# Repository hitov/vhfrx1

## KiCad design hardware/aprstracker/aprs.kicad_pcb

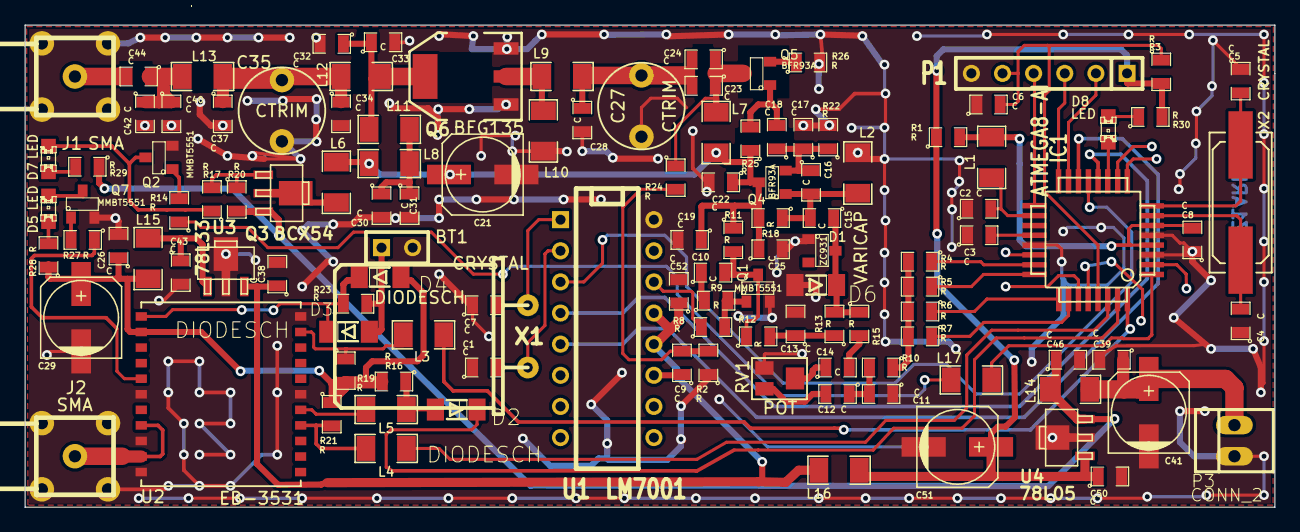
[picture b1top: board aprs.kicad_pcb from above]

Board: 2 copper layers, 102.0 x 39.3 mm, 122 parts (0 on the bottom side), 74 nets.

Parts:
ASTUB: VAL**; ASTUB
BT1: BATTERY; SIL-2
C1, C2, C3, C4, C5, C6, C7, C8, C9, C10, C11, C12, C13, C14, C15, C16, C17, C18, C19, C22, C23, C24, C25, C26, C28, C30, C31, C32, C33, C34, C37, C38, C39, C40, C42, C43, C44, C46, C50, C52: C; SM0805
C21, C41, C51: CAPAPOL; c_elec_6.3x4.5
C27, C35: CTRIM; TSC6
C29: CP1; c_elec_6.3x4.5
D1: ZC931; SOT23
D2, D3, D4: DIODESCH; MiniMelf
D5, D7, D8: LED; LED-0805
D6: VARICAP; MiniMelf
IC1: ATMEGA8-AI; TQFP32
J1, J2: SMA
L1, L2, L3, L4, L5, L6, L7, L8, L9, L10, L11, L12, L13, L14, L15, L16, L17: INDUCTOR; SM1206
P1: CONN_6; SIL-6
P3: CONN_2; PINHEAD1-2
Q1, Q2, Q7: MMBT5551; SOT23
Q3: BCX54; sot89
Q4, Q5: BFR93A; SOT23
Q6: BFG135; SOT223
R1, R2, R3, R4, R5, R6, R7, R8, R9, R10, R11, R12, R13, R14, R15, R16, R17, R18, R19, R20, R21, R22, R23, R24, R25, R26, R27, R28, R29, R30: R; SM0805
RV1: POT; MVR34
U1: LM7001; DIP-16__300
U2: EB-3531
U3: 78L33; sot89
U4: 78L05; sot89
X1: CRYSTAL; HC-18UH
X2: CRYSTAL; Q_49U3HMS

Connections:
3V3: C26.1, C29.1, D4.1, L15.2, R16.2, R19.2, R21.1, R28.1, U2.12
+5V: C38.1, C52.1, L16.2, U1.12, U1.13, U3.3
AUDIO: C11.2, C12.1, R10.2
CE: IC1.13, U1.3
CL: IC1.12, U1.4
DATA: IC1.14, U1.5
GND: BT1.2, C1.1, C2.1, C3.1, C4.1, C5.1, C6.1, C7.1, C8.1, C11.1, C13.2, C17.2, C19.2, C21.2, C22.2, C25.2, C26.2, C27.2, C28.2, C29.2, C30.2, C31.2, C32.2, C33.2, C34.2, C35.2, C37.2, C38.2, C39.2, C40.2, C41.2, C42.2, C43.2, C46.2, C50.2, C51.2, C52.2, D1.1, D6.1, IC1.3, IC1.5, IC1.21, J1.2, J1.3, J1.4, J1.5, J2.2, J2.3, J2.4, J2.5, L2.1, L10.2, P1.6, P3.1, Q1.2, Q2.2, Q6.1, Q6.3, Q7.2, R2.1, R22.2, R26.2, RV1.1, U1.16, U2.10, U2.18, U2.20, U2.21, U2.22, U3.2, U4.2
unnamed: R27.1, U2.15
unnamed: Q7.1, R27.2
unnamed: L3.2, R19.1, U2.9
unnamed: C39.1, C41.1, L14.1, P3.2
unnamed: L5.2, U2.5
unnamed: L4.2, R21.2, U2.4
unnamed: D3.2, D4.2, R23.1, U2.11
unnamed: BT1.1, D3.1, R23.2
unnamed: C43.1, L15.1, U3.1
unnamed: C40.1, C42.1, C44.1, L13.2
unnamed: C23.2, C24.2, C27.1, C28.1, L9.1
unnamed: C7.2, U1.1, X1.1
unnamed: C9.1, U1.11
unnamed: C13.1, R12.2, R13.1
unnamed: Q3.1, R17.2, R20.1
unnamed: C10.1, R9.1
unnamed: R8.1, U1.14
unnamed: IC1.26, R7.1
unnamed: C5.2, IC1.8, X2.2
unnamed: IC1.23, R4.1
unnamed: IC1.24, R5.1
unnamed: IC1.25, R6.1
unnamed: C3.2, IC1.20
unnamed: L17.2, R14.1
unnamed: C14.2, R15.2
unnamed: C14.1, RV1.2
unnamed: IC1.15, P1.2
unnamed: IC1.16, P1.3
unnamed: IC1.17, P1.4
unnamed: C6.2, IC1.29, P1.5, R3.1
unnamed: C4.2, IC1.7, X2.1
unnamed: L9.2, L10.1, Q6.2
unnamed: C18.2, Q5.1, R25.2
unnamed: Q5.2, R26.1
unnamed: C15.1, D1.3, D6.2, R13.2, R15.1
unnamed: D8.1, R30.1
unnamed: D8.2, IC1.11
unnamed: C23.1, C24.1, L7.2, Q5.3, R24.1
unnamed: D5.2, Q7.3
unnamed: Q2.1, R14.2
unnamed: D7.2, Q2.3, R17.1
unnamed: D7.1, R29.2
unnamed: L6.1, Q3.2
unnamed: C44.2, J1.1
unnamed: C9.2, R2.2, R24.2
unnamed: J2.1, U2.17, U2.19
unnamed: C8.2, IC1.4, IC1.6, L1.2, R1.2
unnamed: C2.2, IC1.18, L1.1
unnamed: R4.2, R5.2, R6.2, R7.2, R10.1
unnamed: Q1.1, R8.2, R9.2
unnamed: C10.2, Q1.3, R11.2, R12.1
unnamed: C15.2, C16.2, L2.2, Q4.1, R18.1
unnamed: C16.1, C17.1, C18.1, Q4.2, R22.1
unnamed: C12.2, RV1.3
unnamed: C1.2, U1.2, X1.2
unnamed: C34.1, C35.1, C37.1, L12.2, L13.1
unnamed: C32.1, C33.1, L11.2, L12.1, Q6.4
unnamed: C19.1, C21.1, C22.1, C25.1, L6.2, L7.1, L8.1, Q4.3, R11.1, R18.2, R25.1
unnamed: C30.1, C31.1, L8.2, L11.1
unnamed: D2.1, L5.1, R16.1
unnamed: D5.1, R28.2
RF_EN: IC1.1, L17.1
RF_PWR: IC1.32, L3.1
RXD: IC1.30, L4.1
TXD: D2.2, IC1.31
VCC: C50.1, C51.1, L16.1, P1.1, R1.1, R3.2, R30.2, U4.1
VDD: C46.1, L14.2, Q3.3, R20.2, R29.1, U4.3

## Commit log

2013-01-09 VHF Radio - Initial commit
2013-01-09 Add .gitignore
2013-01-09 LEDS On
2013-01-09 Make Leds to blink
2013-05-11 Add lm7001 driver (initial non tested)
2013-05-11 LM7001 driver update and build conditions
2013-05-18 Add LTspice VCO simulation
2013-05-26 [HW] New schematics for aprs tracker
2013-05-27 [HW] Update schematics
2013-05-31 [HW] Schematic update
2013-05-31 [HW] Kicad project adjustments
2013-06-03 [HW] Schematics/footprints update
2013-06-04 [HW] Update pcb, rearrange components
2013-11-24 [HW] Add uncommited changes / PCB updates
2013-11-24 [HW] route pcb
2013-11-27 [HW] PCB Ground plane update
2013-11-30 [HW] Fix GPS footprint and pcb
2013-11-30 [HW] PCB - rearrange designators
2013-11-30 [HW] PCB - minor adjustments
2013-11-30 [HW] PCB - Fix DRC errors
2013-12-02 [HW] Update pcb/sch/gps
2013-12-02 [HW] remove aprs.bak
2013-12-03 [HW] Add schematics values
2013-12-03 [HW] Update schematics element values, add .gitignore rules, add files
2013-12-08 [HW] - Fix schematics of collpits oscillator and add values
2013-12-15 [HW] Update schematic elements values
2013-12-15 [HW] Update values. Add capacitor to suppress negative feedback
2013-12-15 [HW] Add simulations for vco an tx
2014-01-04 Update sch elements values
2014-01-04 [HW] Generate schematics pdf file
2014-01-04 [HW] Fix element values
